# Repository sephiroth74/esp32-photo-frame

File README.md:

# ESP32 E-Paper Photo Frame

<p>
  <center></center>
</p>

<p>
  <center>

  </center>
</p>

**ESP32 E-Paper Photo Frame** is an open-source project designed to turn a low-power e-paper display into a smart, battery-efficient digital photo frame. Built around the ESP32 ecosystem, it offers a seamless way to display your memories using modern connectivity or local storage.

It allows to display images from different types of data providers like:
  * Shared Google Drive folders
  * Internal SD Card
  * Upload directly into the board via Wifi and your phone

The project also provides a **complete hardware solution**:
- **3D Printable Enclosure**: A custom-designed case available in [esp32-photo-frame.3mf](assets/printables/esp32-photo-frame.3mf).
- **Assembly Guide**: Comprehensive instructions for assemblying the device. See the [Assembly Guide](docs/assembly_guide.pdf)
- **Hardware Schematics**: See the [Schematics](docs/pros3d_schematics.pdf) on how to connect the hardware components.

## Hardware Requirements

To build this project, you will need the following core components. A detailed bill of materials is available in the [Assembly Guide](docs/assembly_guide.pdf).

### Essential Components
| Component           | Recommendation                                                                          | Notes                                            |
| ------------------- | --------------------------------------------------------------------------------------- | ------------------------------------------------ |
| **Microcontroller** | [Unexpected Maker ProS3-D](https://unexpectedmaker.com/shop.html#!/ProS3-D/p/759221737) | ESP32-S3 with PSRAM (Required for image buffer)  |
| **Display**         | [Good Display 7.3" ACeP](https://www.good-display.com/blank7.html?productId=533)        | 800×480, 6-Color (GDEP073E01)                    |
| **Adapter**         | [DESPI-C73](https://www.good-display.com/product/522.html)                              | Connection interface for the display             |
| **Storage**         | [Adafruit MicroSD SPI/SDIO](https://learn.adafruit.com/adafruit-microsd-spi-sdio)       | High-speed SDIO support for faster image loading |
| **Battery**         | 3.7V LiPo (5000mAh+)                                                                    | Required for portable operation                  |

### Key Features

- **Ultra-Low Power**: Designed for longevity, the frame enters deep sleep between updates, lasting months on a standard LiPo battery.
- **E-Paper Optimized**: Leverages multiple dithering algorithms (Floyd-Steinberg, Atkinson, etc.) and a custom 6-color palette (via `.pfr1` format) to transform any image into a stunning e-ink display.
- **Smart & Autonomous**:
  - **Cloud Mode**: Connects to Google Drive to fetch and display random images at set intervals.
  - **Offline Mode**: Cycles through images stored locally on the SD Card.
  - **Local WiFi Mode**: Functions as a static display, updated instantly via the mobile or desktop app.
  - **Night Mode**: Automatically pauses updates during sleeping hours to save energy.
  - **Smart Cropping**: Integrated AI (InsightFace) detects faces to automatically center and crop images for the best composition.
- **Zero-Recompile Config**: All settings (WiFi, schedules, refresh intervals) are managed via a simple `config.json` file on the SD card—no programming knowledge required to tweak settings.

---

### Operating Modes

| Mode            | Image Source          | Update Type      | Main Notes                                     |
| --------------- | --------------------- | ---------------- | ---------------------------------------------- |
| Cloud Mode      | Google Drive          | Scheduled        | Requires Google Drive and WiFi configuration   |
| Offline Mode    | Internal SD Card      | Scheduled/manual | Works without network connection               |
| Local WiFi Mode | Upload via WiFi (App) | Instant/manual   | Requires firmware build with WebServer enabled |
| Night Mode      | All                   | Night pause      | Suspends updates to save power                 |

---
## Architecture Overview

The system operates on a clear pipeline:
1.  **Input**: Images are taken from your phone, computer, sdcard or cloud storage.
2.  **Processing**: Images are resized, dithered, and converted into the efficient [**`.pfr1`**](docs/BINARY_FILE_FORMAT.md) binary format by the provided tools (Rust CLI / Desktop App / Mobile App).
3.  **Transfer**: Processed files are moved to the frame via SD Card, Google Drive, or WiFi.
4.  **Display**: The ESP32 wakes up, loads the image, renders it to the e-paper screen, and returns to deep sleep.

## Project Structure

 - `platformio`: The main ESP32 firmware source code (C++)
 - `rust`
   - `processor`: This is the main desktop command line utility used to optimize and convert your images into the dedicated `.pfr1` file format used by the ESP32 board. It's a rust cli, which can be compiled for almost all operating systems. [Read more here](rust/processor/README.md)
   - `ws_client`: Small rust command line utility used to upload the `.pfr1` images into the ESP32 board, when it is compiled to accept images from Wifi
 - `flutter`:
   - `desktop`: Cross platform desktop GUI which can be used to interface with the rust processor cli. It can also be used to upload images into the board when the Wifi option is enabled on the ESP32.
   - `mobile`: iOS and Android app used to convert and upload your images into the ESP32 board when the Wifi option is enabled. 
 - `docs`: Contains most of the the documentation

## Quick Start

Follow these steps to get your frame running:

There are basically 2 configurations for the ESP32:

 - **DEFAULT**: It will display images from Google Drive or the internal SD Card based on the configuration stored into the `config.json` in the root of the SD Card.
 - **WIFI**: It will display the images using an internal WebServer to which devices can connect and upload images into. This configuration can be enabled by setting the `ENABLE_WEBSERVER_DATAPROVIDER` constant to the platformio.ini environment

### Firmware & Hardware
1.  **Assemble**: Follow the [Assembly Guide](docs/assembly_guide.pdf) to build the hardware.
2.  **Flash Firmware**:
    - Install **Visual Studio Code** and the **PlatformIO** extension.
    - Open the `platformio/` folder.
    - Select your board (e.g., `pros3d_unexpectedmaker`) and click **Build** and **Upload**.
    - *See [Firmware Overview](docs/FIRMWARE_OVERVIEW.md) for detailed instructions.*

### Configuration (SD Card)
1.  Format a microSD card (FAT32).
2.  Create a `config.json` file in the root (see the [example_config.json](platformio/example_config.json))
3.  Add your WiFi and Component settings.
    ```json
    {
      "wifi": [{"ssid": "MyWifi", "password": "pass"}],
      "sd_card_config": {"enabled": true, "directories": ["/images"]},
      "google_drive_config": {"enabled": false}
    }
    ```
> See [Configuration Reference](docs/CONFIG_REFERENCE.md) for the complete `config.json` reference.

## Configuration (Google Drive)

In order to enable the Google Drive dataprovider, your config.json should look something like this:

```json
{
  ...
  "google_drive_config": {
    "enabled": true,
    "authentication": {
      "service_account_email": "your-service-account@your-project.iam.gserviceaccount.com",
      "private_key_pem": "-----BEGIN PRIVATE KEY-----\nYOUR_PRIVATE_KEY_CONTENT_HERE\n-----END PRIVATE KEY-----\n",
      "client_id": "your-client-id"
    },
    "drive": {
      "folder_ids": [
        "your-google-drive-folder-id-1",
        "your-google-drive-folder-id-2",
      ],
      "root_ca_path": "/certs/google_root_ca.pem",
      "list_page_size": 100,
      "use_insecure_tls": false
    },
    ...
  }
  ...
}
```
> Read more how to setup your Google Drive here: [GOOGLE DRIVE.md](docs/GOOGLE_DRIVE.md)

### Image Processing

The ESP32 board requires images in the custom `.pfr1` format (read the file format specifications here: [BINARY FILE FORMAT.md](docs/BINARY_FILE_FORMAT.md)). Use one of the included tools in order to create the file:

- **Desktop App (GUI)**: Drag-and-drop tool for macOS/Windows/Linux.  
  [Desktop App Guide](flutter/desktop/README.md)
- **Mobile App**: Process and upload directly from your phone.  
  [Mobile App Guide](flutter/mobile/README.md)
- **CLI Tool**: Power-user tool for batch processing.  
  [Rust Tools Overview](docs/RUST_OVERVIEW.md)

For instance, with the included rust cli, it can be done like this:

```bash
$ cargo run -- -i "~/photos/google_photos/" -o ~/Desktop/outputs/ -t six-colors --orientation 1 --output-format pfr1,jpg --dithering atkinson --dither-strength 100 --contrast 10 --brightness 40 --saturation 100 --auto-color --detect-people --confidence=0.5 --annotate --font Geneva --font-size 20 --annotation_background '#40000000' --no-pairing --extensions jpg,jpeg,png,heic,webp,tiff --verbose
```

When `detect-people` is set, the tool will automatically resize and crop the image based on the person found in the picture.

> Note that [imagemagick](https://imagemagick.org) is required for some operations.

### Upload Images
Choose your preferred method:
- **SD Card**: Copy `.pfr1` files directly to the SD card.
  [Enable the SD Card dataprovider](docs/CONFIG_REFERENCE.md)
- **Google Drive**: Upload files to your Drive folder.  
  [Google Drive Setup](docs/GOOGLE_DRIVE.md)
- **WiFi**: Use the Mobile or Desktop App to upload images wirelessly (requires `ENABLE_WEBSERVER_DATAPROVIDER` firmware build).  
  [WiFi Guide](docs/WIFI.md)

For detailed technical documentation, please refer to the `docs/` folder.

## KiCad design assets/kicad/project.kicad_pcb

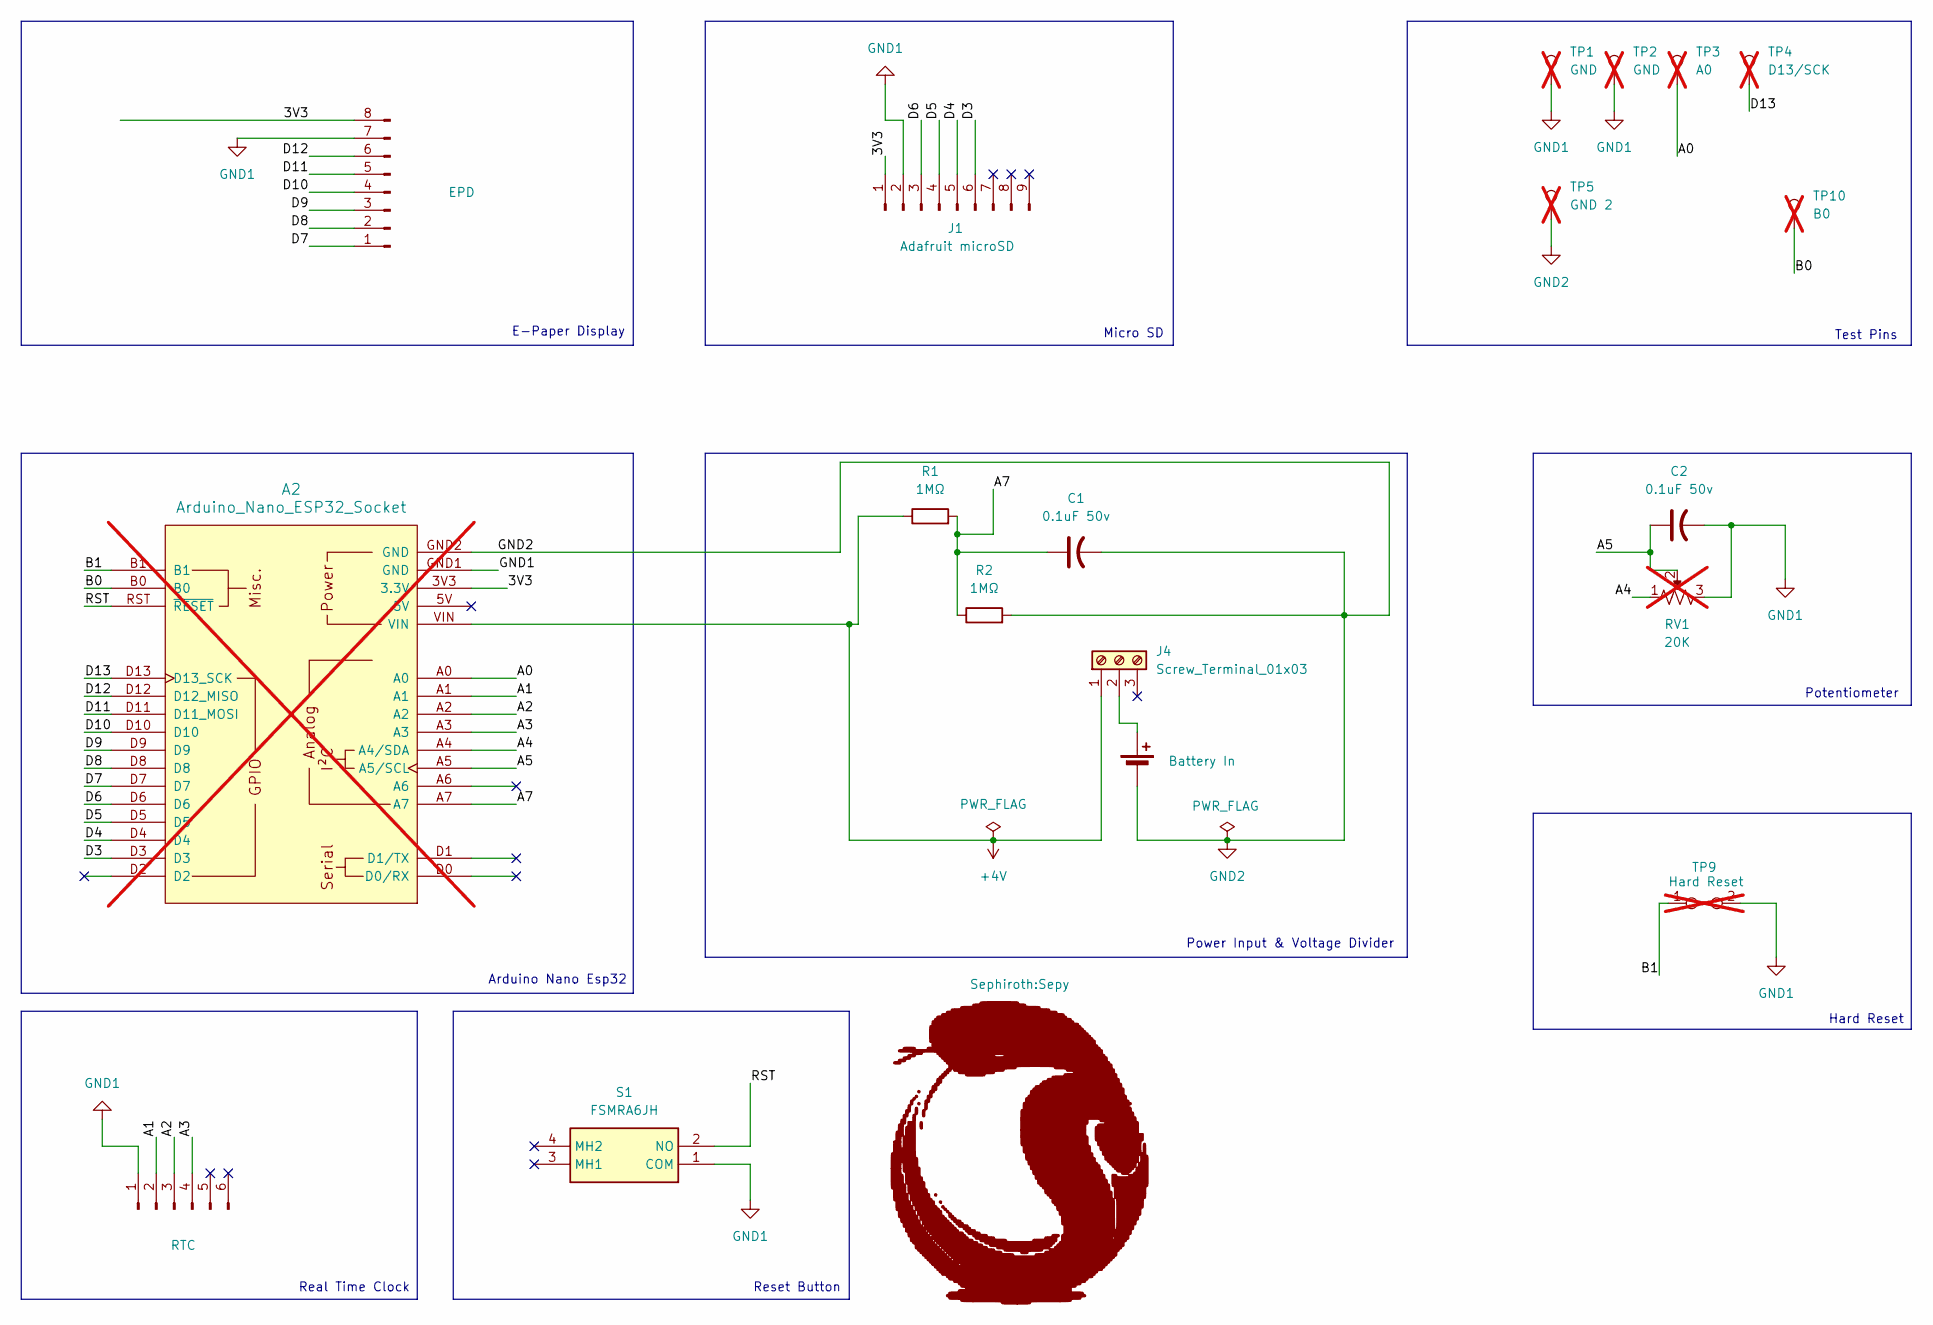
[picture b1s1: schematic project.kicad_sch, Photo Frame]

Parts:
A2: Arduino_Nano_ESP32_Socket; not fitted
BT1: Battery In; JST_PH_S2B-PH-K_1x02_P2.00mm_Horizontal
C1, C2: 0.1uF 50v; CP_Radial_D4.0mm_P1.50mm
J1: Adafruit microSD; PinHeader_1x09_P2.54mm_Vertical
J2: EPD; PinHeader_1x08_P2.54mm_Vertical
J3: RTC; PinHeader_1x06_P2.54mm_Vertical
J4: Screw_Terminal_01x03; TerminalBlock_MaiXu_MX126-5.0-03P_1x03_P5.00mm
R1, R2: 1MΩ; R_Axial_DIN0207_L6.3mm_D2.5mm_P7.62mm_Horizontal
RV1: 20K; Potentiometer_Alps_RK163_Single_Horizontal; not fitted
S1: FSMRA6JH; P&B Tactile Button Right Angle - FSMRA6JH; Mouser Part Number 655-FSMRA6JH
TP1, TP2: GND; SolderWire-0.5sqmm_1x01_D0.9mm_OD2.3mm; not fitted
TP3: A0; SolderWire-0.5sqmm_1x01_D0.9mm_OD2.3mm; not fitted
TP4: D13/SCK; SolderWire-0.5sqmm_1x01_D0.9mm_OD2.3mm; not fitted
TP5: GND 2; SolderWire-0.5sqmm_1x01_D0.9mm_OD2.3mm; not fitted
TP9: Hard Reset; TestPoint_2Pads_Pitch2.54mm_Drill0.8mm; not fitted
TP10: B0; SolderWire-0.5sqmm_1x01_D0.9mm_OD2.3mm; not fitted

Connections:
+4V: A2.VIN, J4.1, R1.1
/3V3: A2.3V3 (3.3V), J1.1, J2.8
/A0: A2.A0, TP3.1
/A1: A2.A1, J3.2
/A2: A2.A2, J3.3
/A3: A2.A3, J3.4
/A4: A2.A4 (A4/SDA), RV1.1
/A5: A2.A5 (A5/SCL), C2.1, RV1.2
/A7: A2.A7, C1.1, R1.2, R2.1
/B0: A2.B0, TP10.1
/B1: A2.B1, TP9.1
/D3: A2.D3, J1.6
/D4: A2.D4, J1.5
/D5: A2.D5, J1.4
/D6: A2.D6, J1.3
/D7: A2.D7, J2.1
/D8: A2.D8, J2.2
/D9: A2.D9, J2.3
/D10: A2.D10, J2.4
/D11: A2.D11 (D11_MOSI), J2.5
/D12: A2.D12 (D12_MISO), J2.6
/D13: A2.D13 (D13_SCK), TP4.1
/RST: A2.RST (~RESET), S1.2 (NO)
GND1: A2.GND1 (GND), C2.2, J1.2, J2.7, J3.1, RV1.3, S1.1 (COM), TP1.1, TP2.1, TP9.2
GND2: A2.GND2 (GND), BT1.2 (-), C1.2, R2.2, TP5.1
unnamed: BT1.1 (+), J4.2

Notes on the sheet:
Power Input & Voltage Divider
Micro SD
Hard Reset
E-Paper Display
Real Time Clock
Potentiometer
Arduino Nano Esp32
Reset Button
Test Pins

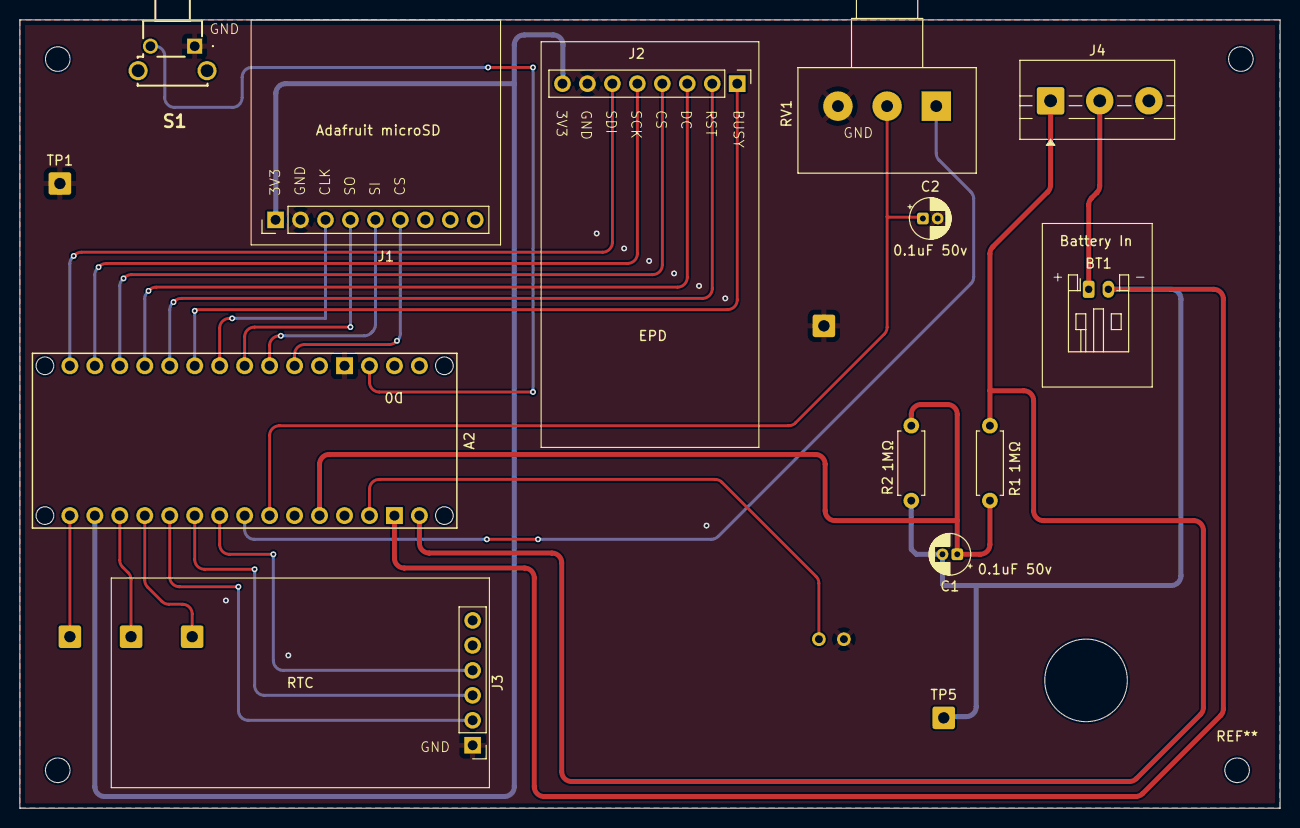
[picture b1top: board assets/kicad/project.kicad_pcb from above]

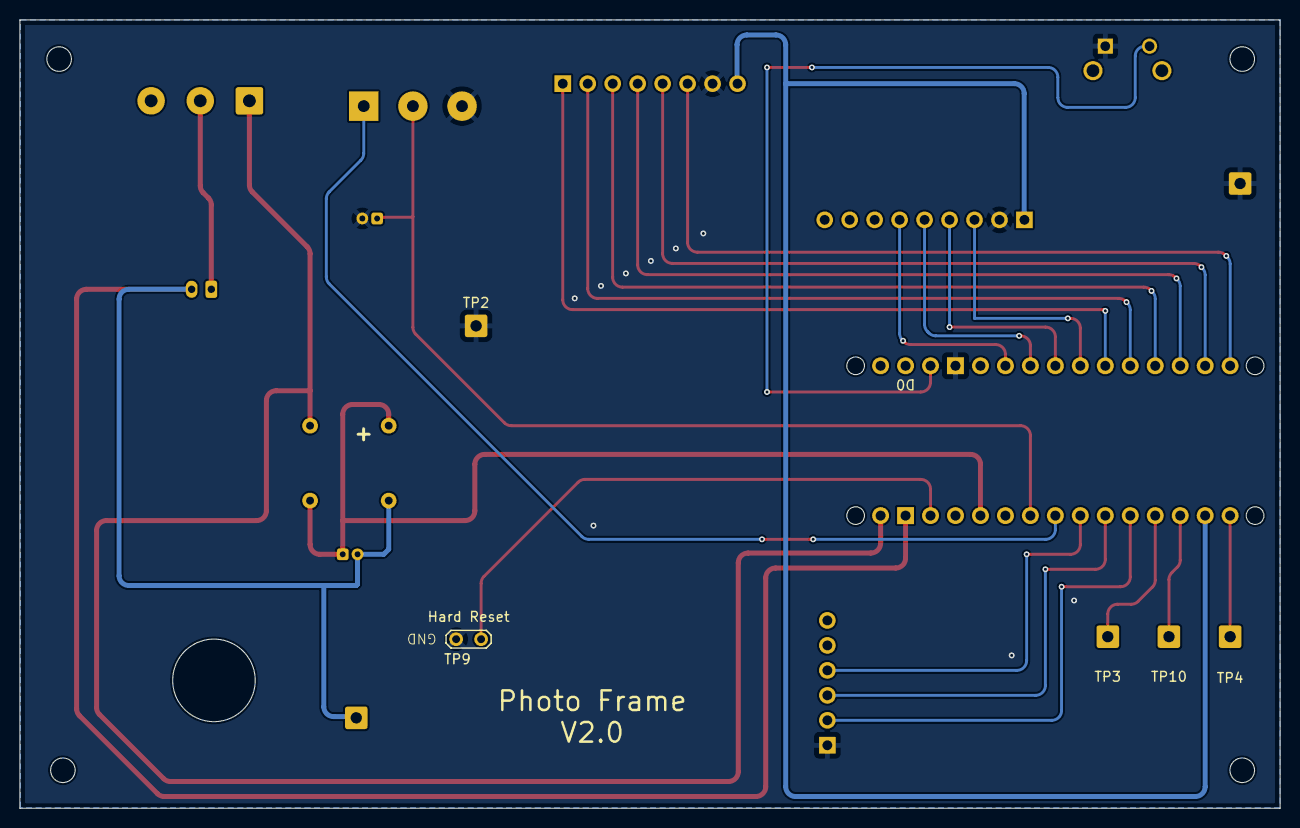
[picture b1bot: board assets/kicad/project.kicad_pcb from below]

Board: 2 copper layers, 128.2 x 80.2 mm, 19 parts (5 on the bottom side), 26 nets.

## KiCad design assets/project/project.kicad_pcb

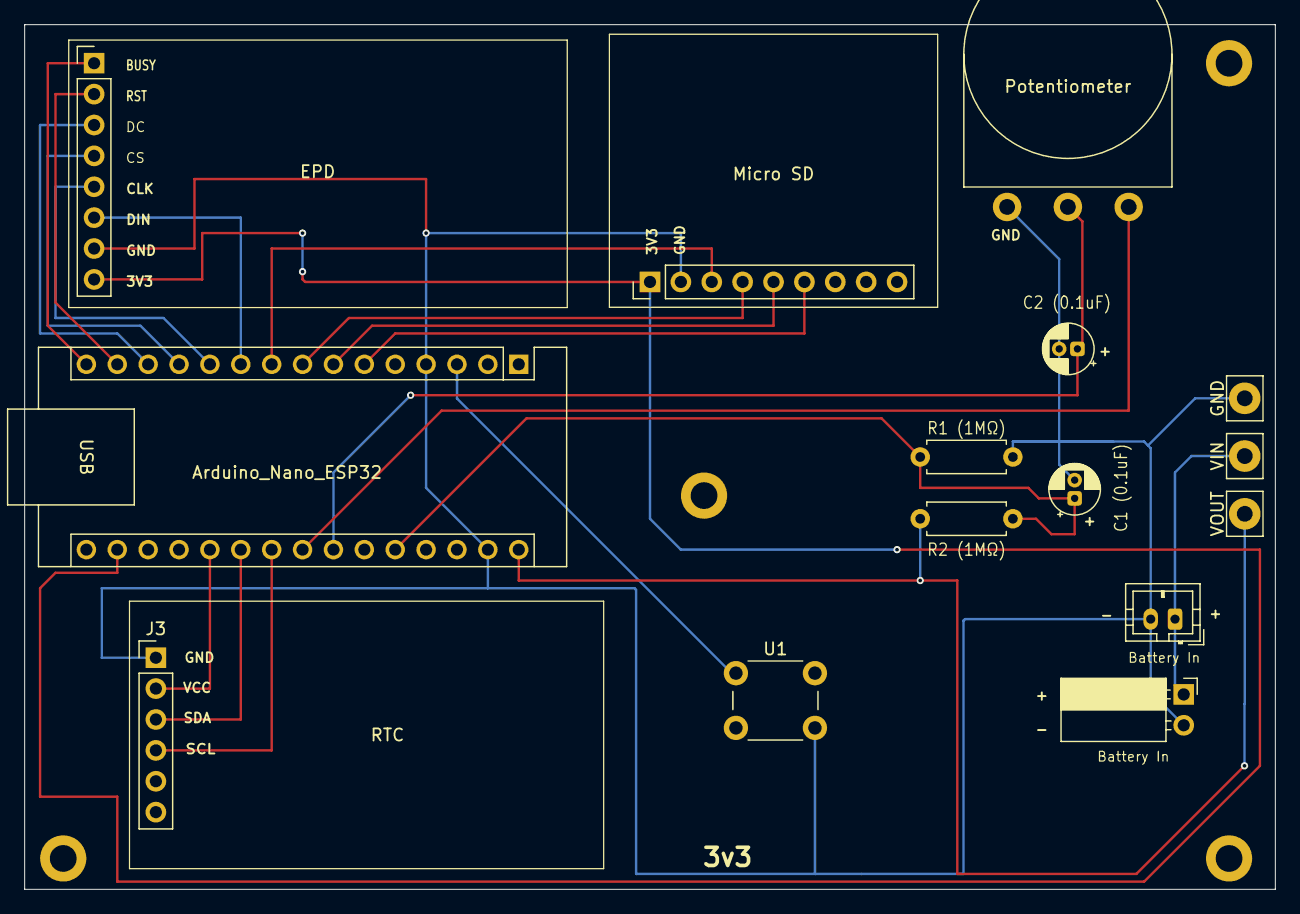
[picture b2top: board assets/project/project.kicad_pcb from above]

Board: 2 copper layers, 102.9 x 71.1 mm, 15 parts (0 on the bottom side), 20 nets.

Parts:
A1: Arduino_Nano_ESP32; Arduino_Nano
BT1: Battery In; JST_PH_B2B-PH-K_1x02_P2.00mm_Vertical
C1 (0.1uF), C2 (0.1uF): 0.1uF; CP_Radial_D4.0mm_P1.50mm
GND: GND; Pin_D1.3mm_L10.0mm_W3.5mm_Flat
J1: Micro SD; PinHeader_1x09_P2.54mm_Vertical
J2: EPD; PinHeader_1x08_P2.54mm_Vertical
J3: RTC; PinHeader_1x06_P2.54mm_Vertical
J4: Battery In; PinSocket_1x02_P2.54mm_Horizontal
R1 (1MΩ), R2 (1MΩ): R (1M); R_Axial_DIN0207_L6.3mm_D2.5mm_P7.62mm_Horizontal
RV1: Potentiometer; Potentiometer_Omeg_PC16BU_Vertical
U1: Reset; SW_PUSH_6mm
VIN: VIN; Pin_D1.3mm_L10.0mm_W3.5mm_Flat
VOUT: VOUT; Pin_D1.3mm_L10.0mm_W3.5mm_Flat

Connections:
+4V: A1.30 (VIN), BT1.1 (+), J4.1, R2 (1MΩ).1, VIN.1, VOUT.1
GND: A1.4 (GND), A1.29 (GND), BT1.2 (-), C1 (0.1uF).2, C2 (0.1uF).2, GND.1, J1.2, J2.7, J3.1, J4.2, R1 (1MΩ).2, RV1.3, U1.2
unnamed: A1.17 (3V3), J1.1, J2.8
unnamed: A1.20 (A1), J3.2
unnamed: A1.21 (A2), J3.3
unnamed: A1.22 (A3), J3.4
unnamed: A1.26 (A7), C1 (0.1uF).1, R1 (1MΩ).1, R2 (1MΩ).2
unnamed: A1.6 (D3), J1.6
unnamed: A1.7 (D4), J1.5
unnamed: A1.8 (D5), J1.4
unnamed: A1.9 (D6), J1.3
unnamed: A1.10 (D7), J2.6
unnamed: A1.11 (D8), J2.5
unnamed: A1.12 (D9), J2.4
unnamed: A1.13 (D10/CS), J2.3
unnamed: A1.14 (D11/COPI), J2.2
unnamed: A1.15 (D12/CIPO), J2.1
unnamed: A1.24 (SCL/A5), C2 (0.1uF).1, RV1.2
unnamed: A1.23 (SDA/A4), RV1.1
unnamed: A1.3 (~RESET), U1.1

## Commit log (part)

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2025-09-10 icons and fonts
2025-09-10 weather drawing
2025-09-11 photoframe-processor progress bar visual
2025-09-11 use auto colors with imagemagick
2025-09-11 logging
2025-09-11 using littleFs to download final image + logging
2025-09-11 google drive data is mandatory
2025-09-12 copy file to littleFs after it has been downloaded to sdcard
2025-09-12 formatter
2025-09-12 formatted lines
2025-09-12 updated specs
2025-09-12 fritzing file
2025-09-13 refactored the toc download flow, to avoid writing errors on esp32 base
2025-09-13 docs
2025-09-13 completed refactoring
2025-09-13 small optimizations
2025-09-14 missing clear screen on error
2025-09-15 dry run
2025-09-17 always save to littlefs after downloading into the sd card.
2025-09-18 force use littleFS for temporary storage
2025-09-18 updated version and changelog
2025-09-18 still invalid chars when downloading json
2025-09-22 rgb status led max brightness
2025-09-22 added version string in the display
2025-09-22 preparing for ota
2025-09-24 cleaner cleanup process, correct parsing of the weather datetimes, weather display
2025-09-24 optimized partition layout, psram optimization, weather sunrise/sunset correct parsing
2025-09-24 weather display arrangement, main battery flow
2025-09-25 weather design
2025-09-27 unified config
2025-09-27 removed legacy code
2025-09-30 pros3(d) integration
2025-10-02 enabled RTC on feather s3. changed rgb status led flow
2025-10-02 version 0.8.1
2025-10-06 added divider_width and divider_color to image processor
2025-10-07 updated libs
2025-10-08 addressing busy timeout
2025-10-09 debug display
2025-10-09 more testing
2025-10-09 debugging
2025-10-13 battery tests
2025-10-13 test gdrive setup
2025-10-13 potentiometer test
2025-10-14 updated docs
2025-10-19 added 3d models
2025-10-19 images size
2025-10-19 updated 3d model
2025-10-21 resized asset images
2025-12-21 dithering improved for colored images. added support for um pros3[d], added support for sd card SPI
2025-12-21 test dithering
2025-12-22 removing warnings
2025-12-24 using new native format for bin file on 6c display
2025-12-29 using log_* instead of Serial.print*
2025-12-29 removed ota updates
2026-01-01 added multiple wifi networks, removed bmp support
2026-01-01 version bump
2026-01-01 documentation
2026-01-02 removed explain-optimization flag, kept optimization-report table
2026-01-02 fix: call find_subject.py with python3 explicitly instead of relying on shebang
    - Changed Command::new(script_path) to Command::new("python3").arg(script_path)
    - This ensures the script runs with Python 3 regardless of system's default python
    - Fixes people detection not working when system python points to Python 2.7
2026-01-02 renamed --optimization-report to --report and made it work without --auto-optimize
    - Renamed flag from --optimization-report to --report for brevity
    - Report now works with any processing mode, not just auto-optimize
    - Added venv activation support for find_subject.py: uses 'source .venv/bin/activate && script' if venv exists
    - Verbose output already includes detect_people results (person count, confidence, center, offset)
2026-01-02 report now works without auto-optimize and replaces 'Detailed Processing Results'
    - Report table now populates data even when auto-optimize is disabled
    - Shows actual parameters used (dithering, strength, contrast, saturation)
    - Replaces 'Detailed Processing Results' section when --report is enabled
    - When --report is not used, shows simple detailed results as before
    - Verbose mode already shows detect_people results (lines 1479-1506 in mod.rs)
2026-01-02 formatting + rayon subject detection fix
2026-01-04 implementing portrait feature
2026-01-05 multiline error for portrait, disabled separate bus for sdcard on um pros3[d]
2026-01-06 gitignore for the flutter project
2026-01-06 added flutter project
2026-01-06 updated flutter project with the correct bundle identifier + app icon
2026-01-06 deleted rust gui project, changed flutter app icons
2026-01-08 Fix brightness not visible: apply brightness+contrast together
    Fixed issue where brightness adjustments were not visible in output images.
    Problem:
    - Brightness and contrast were applied in two separate ImageMagick calls
    - First call: -brightness-contrast BRIGHTx0
    - Second call: -brightness-contrast 0xCONTRAST
    - The second call with brightness=0 was resetting the brightness from first call
2026-01-08 Add debug logging for brightness/contrast command execution
    Added console output to debug brightness/contrast issues:
    - Prints brightness and contrast values before building command
    - Logs full command line with all arguments
    - Helps identify if values are being passed correctly to Rust processor
2026-01-08 Add auto-color correction toggle to Flutter UI
    Added AppKitSwitch control to enable/disable auto-color correction:
    - Placed before auto-optimize switch (matches processing order)
    - Uses existing autoColorCorrect config field
    - Description: 'Auto-color correction (remove color casts, enhance quality)'
    - Allows users to control whether ImageMagick color correction is applied
2026-01-08 Add verbose logging for brightness/contrast operations
    Added detailed logging to debug brightness/contrast issues:
    - Logs when apply_brightness_adjustment() is called with values
    - Logs when apply_contrast_adjustment() is called with values
    - Shows which implementation is used (ImageMagick vs Rust fallback)
    - Displays the exact ImageMagick command being executed
    - Logs in processing pipeline when brightness/contrast are applied
2026-01-08 WIP: Add brightness to portrait pairs processing (incomplete)
    Added brightness parameter and application to portrait pairs processing
    for both landscape (left/right) and portrait (top/bottom) orientations.
    Changes:
    - Added brightness to tuple declarations for left/right/top/bottom
    - Added brightness application stage between auto-color and contrast
    - Pipeline order: auto-color → brightness → contrast → dithering
2026-01-08 support custom brightness
2026-01-10 removed GxEPD library and using the good display libraries directy with an internal image buffer and a canvas
2026-01-10 error wrapping
2026-01-10 disable_deep_sleep by constant
2026-01-10 renaming
2026-01-11 chore: add config.json.template and update .gitignore
    - Add template file for config.json with placeholder values
    - Update .gitignore to exclude actual config.json but keep template
    - Prevents accidental commit of sensitive credentials
2026-01-11 updated example config
2026-01-12 fix(sd_card): improve SD card stability during TOC building
    - Add delays every 10 files to prevent SD card overload
    - Implement error recovery with retry mechanism (up to 3 attempts)
    - Reduce verbose logging - only log progress every 10 files
    - Flush buffer periodically to ensure data is written
    - Add yield() calls to allow other tasks to run
    These changes should prevent SD card failures during directory iteration,
2026-01-12 fix: add 30-second timeout to lcd_chkstatus to prevent display hang
    - Add timeout check in lcd_chkstatus() loop
    - Exit after 30 seconds if display doesn't respond
    - Log clear error message on timeout
    - Prevents system from hanging indefinitely if display fails
    This should prevent the photo frame from getting stuck if the e-paper
    display becomes unresponsive or has connection issues.
2026-01-12 feat(display): add timing log to lcd_chkstatus function
    - Log total time taken for display to become ready
    - Different log levels based on response time:
    - Info: < 1 second (fast response)
    - Info: 1-5 seconds (normal response)
    - Warning: > 5 seconds (slow response)
    - Error: timeout occurred
2026-01-12 added busy timeout
2026-01-12 people detection embedded into rust, no more python needed
2026-01-12 lint
2026-01-12 feat: Add display power control and remove 7-color support
    Display Power Control Implementation:
    - Add native LDO2 control for ProS3 boards via GPIO17
    - Implement universal P-MOSFET solution for other boards
    - Add power on/off functions in board_util
    - Integrate power phases with SD card operations
    - Power off display during SD operations to avoid SPI conflicts
2026-01-13 updating docs
2026-01-14 better summary for the rust processor. removed "--force" argument
2026-01-15 reformat
2026-01-22 bluetooth image dataprovider
2026-01-22 updated readme requirements
    updated canvas to render bluetooth image, moved some docs
2026-01-22 refactoring + display orientation
2026-01-25 moving the flutter project
2026-01-25 flutter processor + bluetooth upload
2026-01-25 creating the mobile app for bluetooth upload
2026-01-26 changed the bin file format (added header)
2026-01-28 moving to .pfr1 extension for binary files
2026-01-28 fixed image size
2026-01-28 thumbnail provider
2026-01-28 show file preview
2026-01-28 updated infos
2026-01-28 mobile app updates
2026-01-28 language
2026-01-28 clang format
2026-01-28 minor fixes to the clients
2026-01-29 adjusting upload screen
2026-01-29 multiple delete from gallery
2026-01-29 corrected annotation
2026-01-29 removed old android app
2026-01-29 added wakelock
2026-01-29 removed print
2026-01-29 using pfr1 file extension
2026-01-29 validate header file
2026-01-29 parse binary header
2026-01-29 header verification corrected
2026-01-30 updated the 3d model
2026-01-30 removed annotation screen
2026-01-30 correct thumbnail orientation + gallery cache
2026-01-30 multi data provider + multiple folders
2026-01-31 adjusting settings for optimize battery
2026-01-31 copy image buffer
2026-01-31 moved some constants
2026-01-31 added support in google drive for multi folder
2026-01-31 refactoring processor
2026-02-01 discovery + image pairing
2026-02-01 resize + rotate
2026-02-01 color correction
2026-02-01 3d model
2026-02-01 dithering
2026-02-01 fixed annotation
2026-02-01 combine images
2026-02-01 combined images
2026-02-02 using face detection
2026-02-02 small refactoring
2026-02-02 report plain
2026-02-02 added report config
2026-02-02 report json
2026-02-02 json progress
2026-02-02 updating flutter desktop
2026-02-03 using correct temp files
2026-02-03 show correct progress and summary
2026-02-03 removed unused files
2026-02-03 flutter desktop multiplatform
2026-02-03 phase 2
2026-02-03 macos
2026-02-03 linux app
2026-02-03 assets
2026-02-03 implementing the ws
2026-02-04 added qr code for connecting to the device
2026-02-04 styling
2026-02-04 dialogs
2026-02-04 flutter fail messag, rust temp file
2026-02-04 fixed dialog size
2026-02-04 counting failed images
2026-02-04 linux dialog
2026-02-04 json messages
2026-02-04 flutter report
2026-02-04 progress
2026-02-04 format
2026-02-05 added wifi icon, added shutdown command
2026-02-05 wait until image is loaded
2026-02-05 upload session using interactive menu
2026-02-05 removed bluetooth references
2026-02-06 refactoring
2026-02-07 allow string type
2026-02-07 some memory management refactoring
2026-02-07 updating desktop app to support ws upload
2026-02-08 refactoring battery reader
2026-02-08 refactoring flutter app
2026-02-08 linux
2026-02-09 sending board info json type, connect to ws from mobile
2026-02-09 crop and rotate
2026-02-09 appicon + crop screen
2026-02-10 types refactoring, moved to photoframe_lib
2026-02-10 flutter common lib
2026-02-11 apply dithering
2026-02-11 dither strenght
2026-02-11 theme
2026-02-11 timeout on server activity
2026-02-11 implemented Display for DisplayType
2026-02-11 DisplayType display impl
2026-02-11 renamed screen
2026-02-12 upload screen rotation
2026-02-12 restored ios folder
2026-02-12 client disconnection
2026-02-13 navigation
2026-02-13 enable ios dithering
2026-02-13 completed ios app
2026-02-13 added missing requirement for Info.plist
2026-02-13 conditional compilation
2026-02-13 added license
2026-02-13 screenshots
2026-02-13 fixed image magic filters
2026-02-13 fixed processing and uploading of the desktop app
2026-02-13 finish and shutdown the device
2026-02-13 flutter desktop wait until display is ready
2026-02-14 wait until display is ready + annotation fonts
2026-02-14 fixed image magick operations
2026-02-14 updated flutter desktop to meet the rust processor
2026-02-14 removed comment
2026-02-14 ws_client to wait for display to refresh
2026-02-15 working on documentation
2026-02-16 comments
2026-02-21 ip address
2026-02-21 format code
2026-02-28 flutter desktop dependencies
2026-03-03 style
2026-03-04 processor arguments
2026-03-04 set cron
